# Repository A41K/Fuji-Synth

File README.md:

## Fuji Synth
A smaller 12 pad touch synthesizer with 
- 3 rotary encoders
- 2 buttons
- a 0.91 inch screen
- 2 Sliding potentiometers

## PCB

## Schematic

## 3d model

The firmware can be found in /Firmware/Firmware.cpp

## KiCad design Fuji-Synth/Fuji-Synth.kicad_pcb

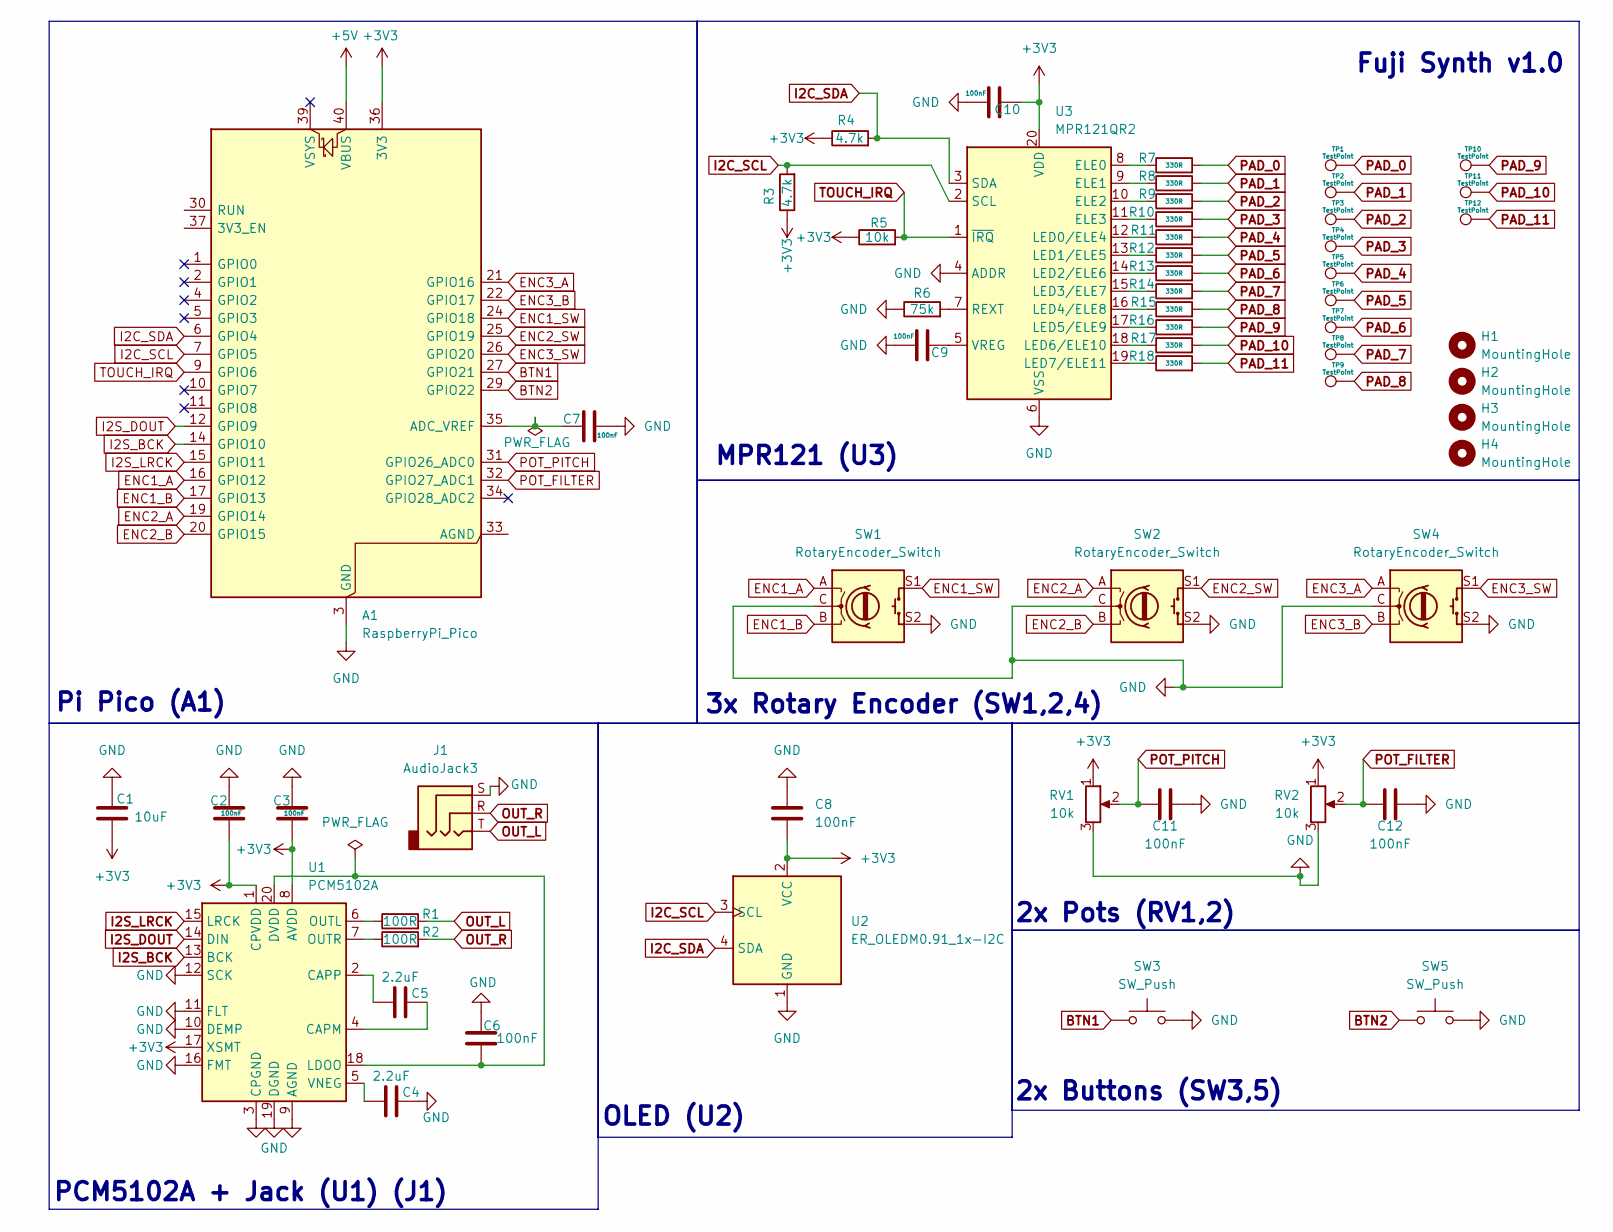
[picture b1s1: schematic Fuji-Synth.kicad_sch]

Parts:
A1: RaspberryPi_Pico; RaspberryPi_Pico_Common_THT
C1: 10uF; C_0805_2012Metric_Pad1.18x1.45mm_HandSolder
C2, C3, C6, C7, C8, C9, C10, C11, C12: 100nF; C_0805_2012Metric_Pad1.18x1.45mm_HandSolder
C4, C5: 2.2uF; C_0805_2012Metric_Pad1.18x1.45mm_HandSolder
H1, H2, H3, H4: MountingHole; MountingHole_2.2mm_M2
J1: AudioJack3; Jack_3.5mm_Lumberg_1503_02_Horizontal
R1, R2: 100R; R_0805_2012Metric_Pad1.20x1.40mm_HandSolder
R3, R4: 4.7k; R_0805_2012Metric_Pad1.20x1.40mm_HandSolder
R5: 10k; R_0805_2012Metric_Pad1.20x1.40mm_HandSolder
R6: 75k; R_0805_2012Metric_Pad1.20x1.40mm_HandSolder
R7, R8, R9, R10, R11, R12, R13, R14, R15, R16, R17, R18: 330R; R_0805_2012Metric_Pad1.20x1.40mm_HandSolder
RV1, RV2: 10k; Potentiometer_Bourns_PTA1543_Single_Slide
SW1, SW2, SW4: RotaryEncoder_Switch; RotaryEncoder_Alps_EC12E-Switch_Vertical_H20mm
SW3, SW5: SW_Push; SW_PUSH_6mm
TP1, TP2, TP3, TP4, TP5, TP6, TP7, TP8, TP9, TP10, TP11, TP12: TestPoint; TouchPad_D12mm
U1: PCM5102A; TSSOP-20_4.4x6.5mm_P0.65mm
U2: ER_OLEDM0.91_1x-I2C
U3: MPR121QR2; UQFN-20_3x3mm_P0.4mm

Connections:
+3V3: A1.36 (3V3), C1.2, C2.2, C3.2, C8.2, C10.2, R3.1, R4.1, R5.1, RV1.1, RV2.1, U1.1 (CPVDD), U1.8 (AVDD), U1.17 (XSMT), U2.2 (VCC), U3.20 (VDD)
+5V: A1.40 (VBUS)
BTN1: A1.27 (GPIO21), SW3.1
BTN2: A1.29 (GPIO22), SW5.1
ENC1_A: A1.16 (GPIO12), SW1.A
ENC1_B: A1.17 (GPIO13), SW1.B
ENC1_SW: A1.24 (GPIO18), SW1.S1
ENC2_A: A1.19 (GPIO14), SW2.A
ENC2_B: A1.20 (GPIO15), SW2.B
ENC2_SW: A1.25 (GPIO19), SW2.S1
ENC3_A: A1.21 (GPIO16), SW4.A
ENC3_B: A1.22 (GPIO17), SW4.B
ENC3_SW: A1.26 (GPIO20), SW4.S1
GND: A1.3 (GND), A1.8 (GND), A1.13 (GND), A1.18 (GND), A1.23 (GND), A1.28 (GND), A1.38 (GND), C1.1, C2.1, C3.1, C4.2, C6.2, C7.1, C8.1, C9.1, C10.1, C11.1, C12.1, J1.S, R6.1, RV1.3, RV2.3, SW1.C, SW1.S2, SW2.C, SW2.S2, SW3.2, SW4.C, SW4.S2, SW5.2, U1.3 (CPGND), U1.9 (AGND), U1.10 (DEMP), U1.11 (FLT), U1.12 (SCK), U1.16 (FMT), U1.19 (DGND), U2.1 (GND), U3.4 (ADDR), U3.6 (VSS)
I2C_SCL: A1.7 (GPIO5), R3.2, U2.3 (SCL), U3.2 (SCL)
I2C_SDA: A1.6 (GPIO4), R4.2, U2.4 (SDA), U3.3 (SDA)
I2S_BCK: A1.14 (GPIO10), U1.13 (BCK)
I2S_DOUT: A1.12 (GPIO9), U1.14 (DIN)
I2S_LRCK: A1.15 (GPIO11), U1.15 (LRCK)
unnamed: A1.35 (ADC_VREF), C7.2
unnamed: C5.2, U1.4 (CAPM)
unnamed: C5.1, U1.2 (CAPP)
unnamed: C6.1, U1.18 (LDOO), U1.20 (DVDD)
unnamed: R1.1, U1.6 (OUTL)
unnamed: R2.1, U1.7 (OUTR)
unnamed: C4.1, U1.5 (VNEG)
unnamed: R7.1, U3.8 (ELE0)
unnamed: R8.1, U3.9 (ELE1)
unnamed: R9.1, U3.10 (ELE2)
unnamed: R10.1, U3.11 (ELE3)
unnamed: R11.1, U3.12 (LED0/ELE4)
unnamed: R12.1, U3.13 (LED1/ELE5)
unnamed: R13.1, U3.14 (LED2/ELE6)
unnamed: R14.1, U3.15 (LED3/ELE7)
unnamed: R15.1, U3.16 (LED4/ELE8)
unnamed: R16.1, U3.17 (LED5/ELE9)
unnamed: R17.1, U3.18 (LED6/ELE10)
unnamed: R18.1, U3.19 (LED7/ELE11)
unnamed: R6.2, U3.7 (REXT)
unnamed: C9.2, U3.5 (VREG)
OUT_L: J1.T, R1.2
OUT_R: J1.R, R2.2
PAD_0: R7.2, TP1.1 (1_1)
PAD_1: R8.2, TP2.1 (1_1)
PAD_2: R9.2, TP3.1 (1_1)
PAD_3: R10.2, TP4.1 (1_1)
PAD_4: R11.2, TP5.1 (1_1)
PAD_5: R12.2, TP6.1 (1_1)
PAD_6: R13.2, TP7.1 (1_1)
PAD_7: R14.2, TP8.1 (1_1)
PAD_8: R15.2, TP9.1 (1_1)
PAD_9: R16.2, TP10.1 (1_1)
PAD_10: R17.2, TP11.1 (1_1)
PAD_11: R18.2, TP12.1 (1_1)
POT_FILTER: A1.32 (GPIO27_ADC1), C12.2, RV2.2
POT_PITCH: A1.31 (GPIO26_ADC0), C11.2, RV1.2
TOUCH_IRQ: A1.9 (GPIO6), R5.2, U3.1 (~IRQ)

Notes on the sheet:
OLED (U2)
Pi Pico (A1)
PCM5102A + Jack (U1) (J1)
2x Pots (RV1,2)
2x Buttons (SW3,5)
MPR121 (U3)
Fuji Synth v1.0
3x Rotary Encoder (SW1,2,4)

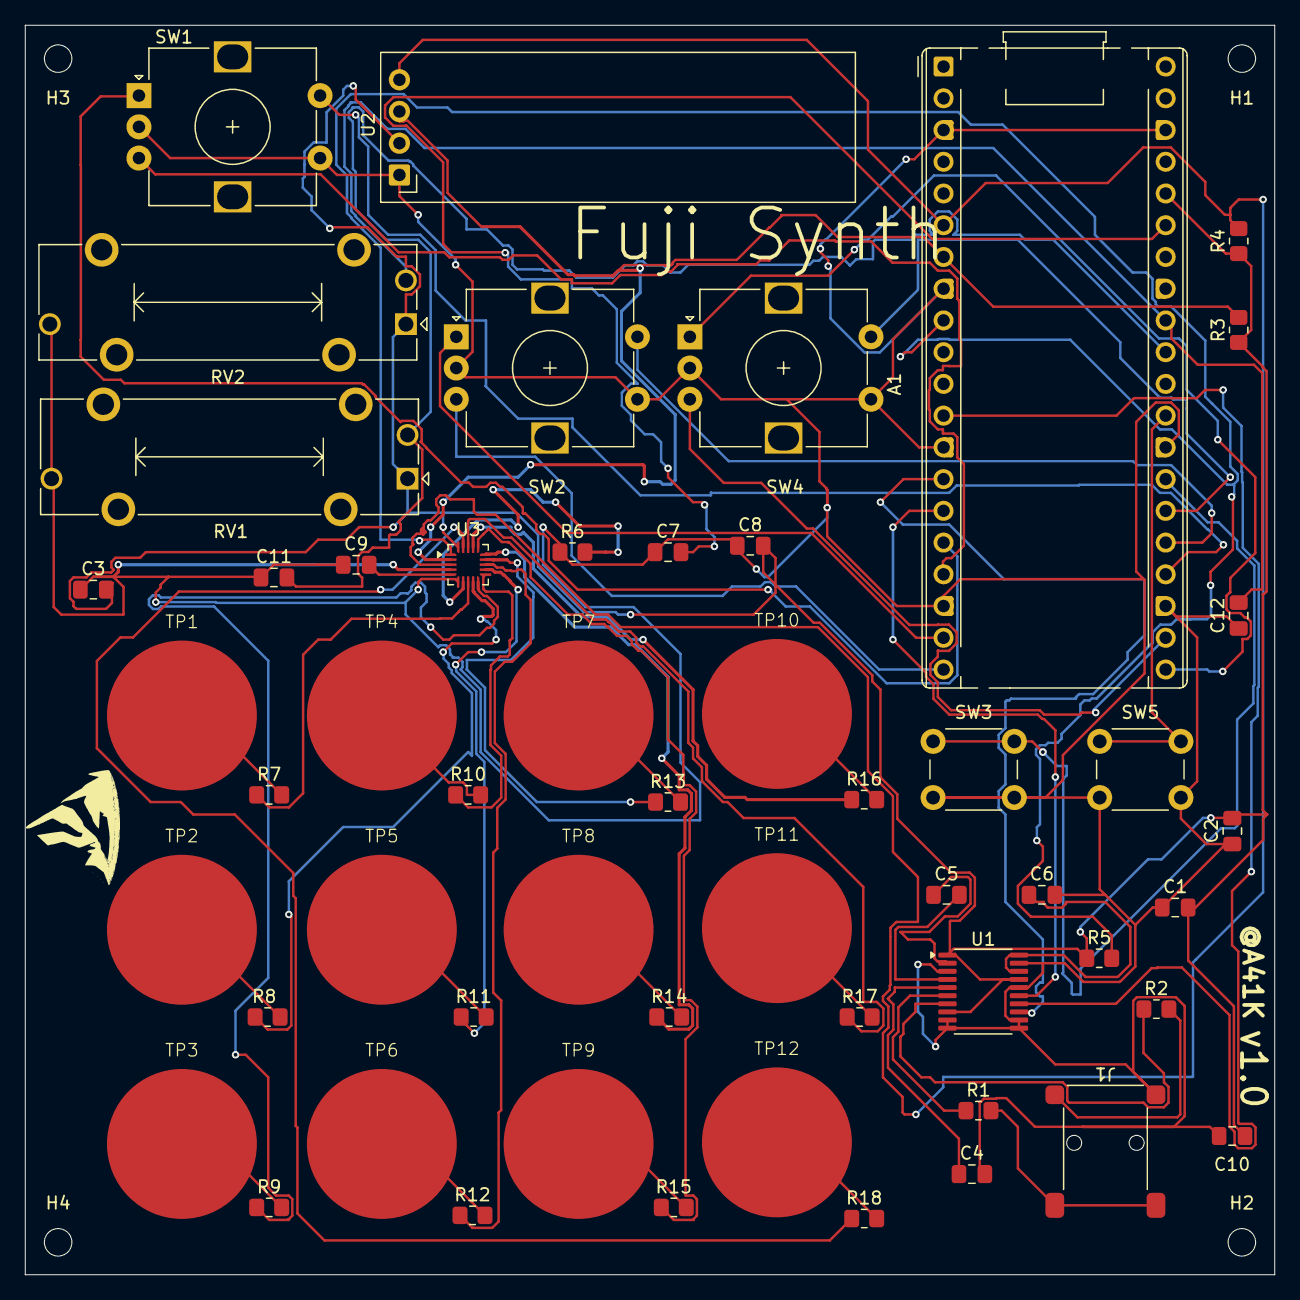
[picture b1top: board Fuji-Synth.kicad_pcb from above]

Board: 2 copper layers, 100.0 x 100.0 mm, 58 parts (0 on the bottom side), 56 nets.

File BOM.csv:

Item,Qty,Supplier,Cost/item,Total Cost,link
RaspberryPi_Pico,1,rpibolt,$8.83,$8.83,https://www.rpibolt.hu/Raspberry-Pi-Pico-2-W-hivatalos-RP235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
10uF,1,,$0.00,$0.00,
100nF,9,,$0.00,$0.00,
2.2uF,2,,$0.00,$0.00,
AudioJack3,1,HQelektronikaa,$1.71,$1.71,https://hqelektronika.hu/csatlakozok/audio-video-csatlakozok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
100R,2,,$0.00,$0.00,
4.7k,2,,$0.00,$0.00,
10k,1,Hestore,$2.54,$2.54,https://www.hestore.hu/prod_10048085.html
75k,1,,$0.00,$0.00,
330R,12,,$0.00,$0.00,
10k,2,,$0.00,$0.00,
RotaryEncoder_Switch,3,,$0.00,$0.00,
PCM5102A,1,modulshop,$5.52,$5.52,https://modulshop.hu/pcm5102a-dac-audio-dekoder-modul-i2s-in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
ER_OLEDM0.91_1x-I2C,1,Microcontroller,$3.04,$3.04,https://www.microcontroller.hu/termek/0-91-oled-kijelzo-feher/
MPR121QR2,1,elektrobot,$3.04,$3.04,https://www.elektrobot.hu/termek.php?filename=5105.html&i=5105
Estimated total shipping,1,,,$0.00,

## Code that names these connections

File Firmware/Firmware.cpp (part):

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#include "hardware/gpio.h"
#include "hardware/sync.h"

#define PIN_I2S_DOUT    9
#define PIN_I2S_BCK     10
#define PIN_I2C_SDA     4
#define PIN_I2C_SCL     5
#define PIN_TOUCH_IRQ   6
#define PIN_POT_PITCH   26
#define PIN_POT_FILTER  27
#define PIN_BTN1        21
#define PIN_BTN2        22

#define MPR_ADDR        0x5A
#define OLED_ADDR       0x3C
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
    struct audio_i2s_config cfg;
    memset(&cfg, 0, sizeof(cfg));
    cfg.data_pin        = PIN_I2S_DOUT;
    cfg.clock_pin_base  = PIN_I2S_BCK;
    cfg.dma_channel     = 0;
    cfg.pio_sm          = 0;

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}

struct Btn { uint8_t pin; bool state; uint32_t t; };
static Btn btns[5] = {{PIN_BTN1,0,0},{PIN_BTN2,0,0},{18,0,0},{19,0,0},{20,0,0}};

static void on_button(int id, uint32_t now) {
    t_misc = now; ui_urgent = true;
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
